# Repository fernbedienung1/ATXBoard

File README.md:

# ATX Breakout board 

## containing blade fuses
because I that I wont be happy with the SMD ones from Dangerous Prototyps ATX board.

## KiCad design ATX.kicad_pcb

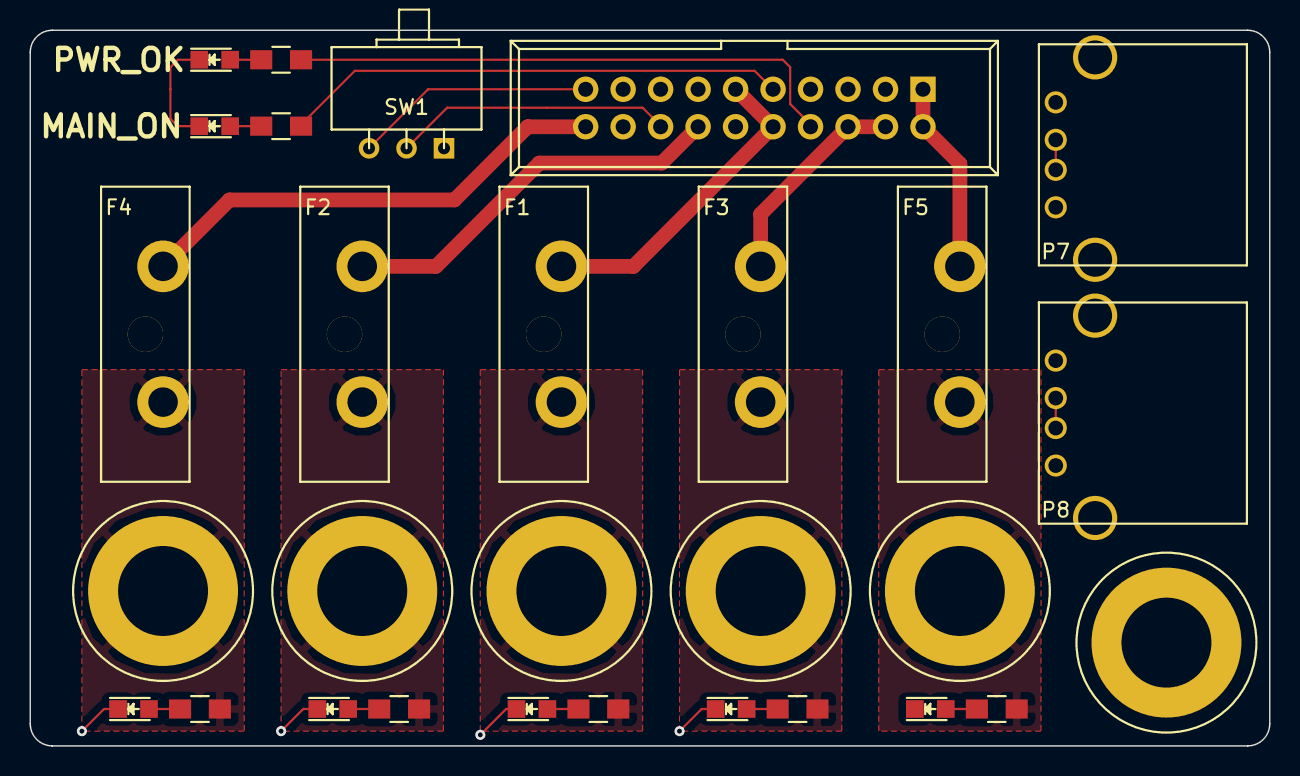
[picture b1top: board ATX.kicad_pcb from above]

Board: 2 copper layers, 84.0 x 48.5 mm, 29 parts (0 on the bottom side), 23 nets.

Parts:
D1, D2, D3, D4, D5: LED_GN; LED_0805
D6, D7: LED; LED_0805
F1, F2, F3, F4, F5: 5A; Fuseholder_ATO_Blade_littlefuse_Pudenz_2_Pin
P1: +12V_OUT; Banana_Jack_1Pin
P2: -12V_OUT; Banana_Jack_1Pin
P3: ATX2.4-IN; IDC_Header_Straight_20pins
P4: +5V_OUT; Banana_Jack_1Pin
P5: -5V_OUT; Banana_Jack_1Pin
P6: +3V3_OUT; Banana_Jack_1Pin
P7, P8: USB_A
P9: GND_OUT; Banana_Jack_1Pin
R1, R2: 1K; R_0805_HandSoldering
R3, R4, R6, R7: 330; R_0805_HandSoldering
R5: 120; R_0805_HandSoldering
SW1: ON/OFF; SW_Micro_SPST_Angled

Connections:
5V_FUSE: F3.2, P4.1, P7.1, P8.1, R3.2
+3.3V: F5.1, P3.1, P3.2, P3.12, P3.13
+5V: F3.1, P3.4, P3.6
+12V: F1.1, P3.10, P3.11
-5V: F4.1, P3.20
-12V: F2.1, P3.14
GND: D1.1, D2.1, D3.1, D4.1, D5.1, D6.1, D7.1, P3.3, P3.5, P3.7, P3.15, P3.17, P3.18, P3.19, P7.4, P8.4, P9.1, SW1.3
MAINS_ON: P3.9, R7.2
unnamed: D1.2, R1.1
unnamed: D2.2, R2.1
unnamed: D3.2, R3.1
unnamed: D4.2, R4.1
unnamed: D5.2, R5.1
unnamed: D6.2, R6.1
unnamed: D7.2, R7.1
unnamed: F1.2, P1.1, R1.2
unnamed: F2.2, P2.1, R2.2
unnamed: F4.2, P5.1, R4.2
unnamed: F5.2, P6.1, R5.2
unnamed: P7.2, P7.3
unnamed: P8.2, P8.3
PWR_OK: P3.8, R6.2
PWR_ON: P3.16, SW1.2

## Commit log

2018-05-15 Initial Commit for GitHub
2018-05-15 and here are the files
